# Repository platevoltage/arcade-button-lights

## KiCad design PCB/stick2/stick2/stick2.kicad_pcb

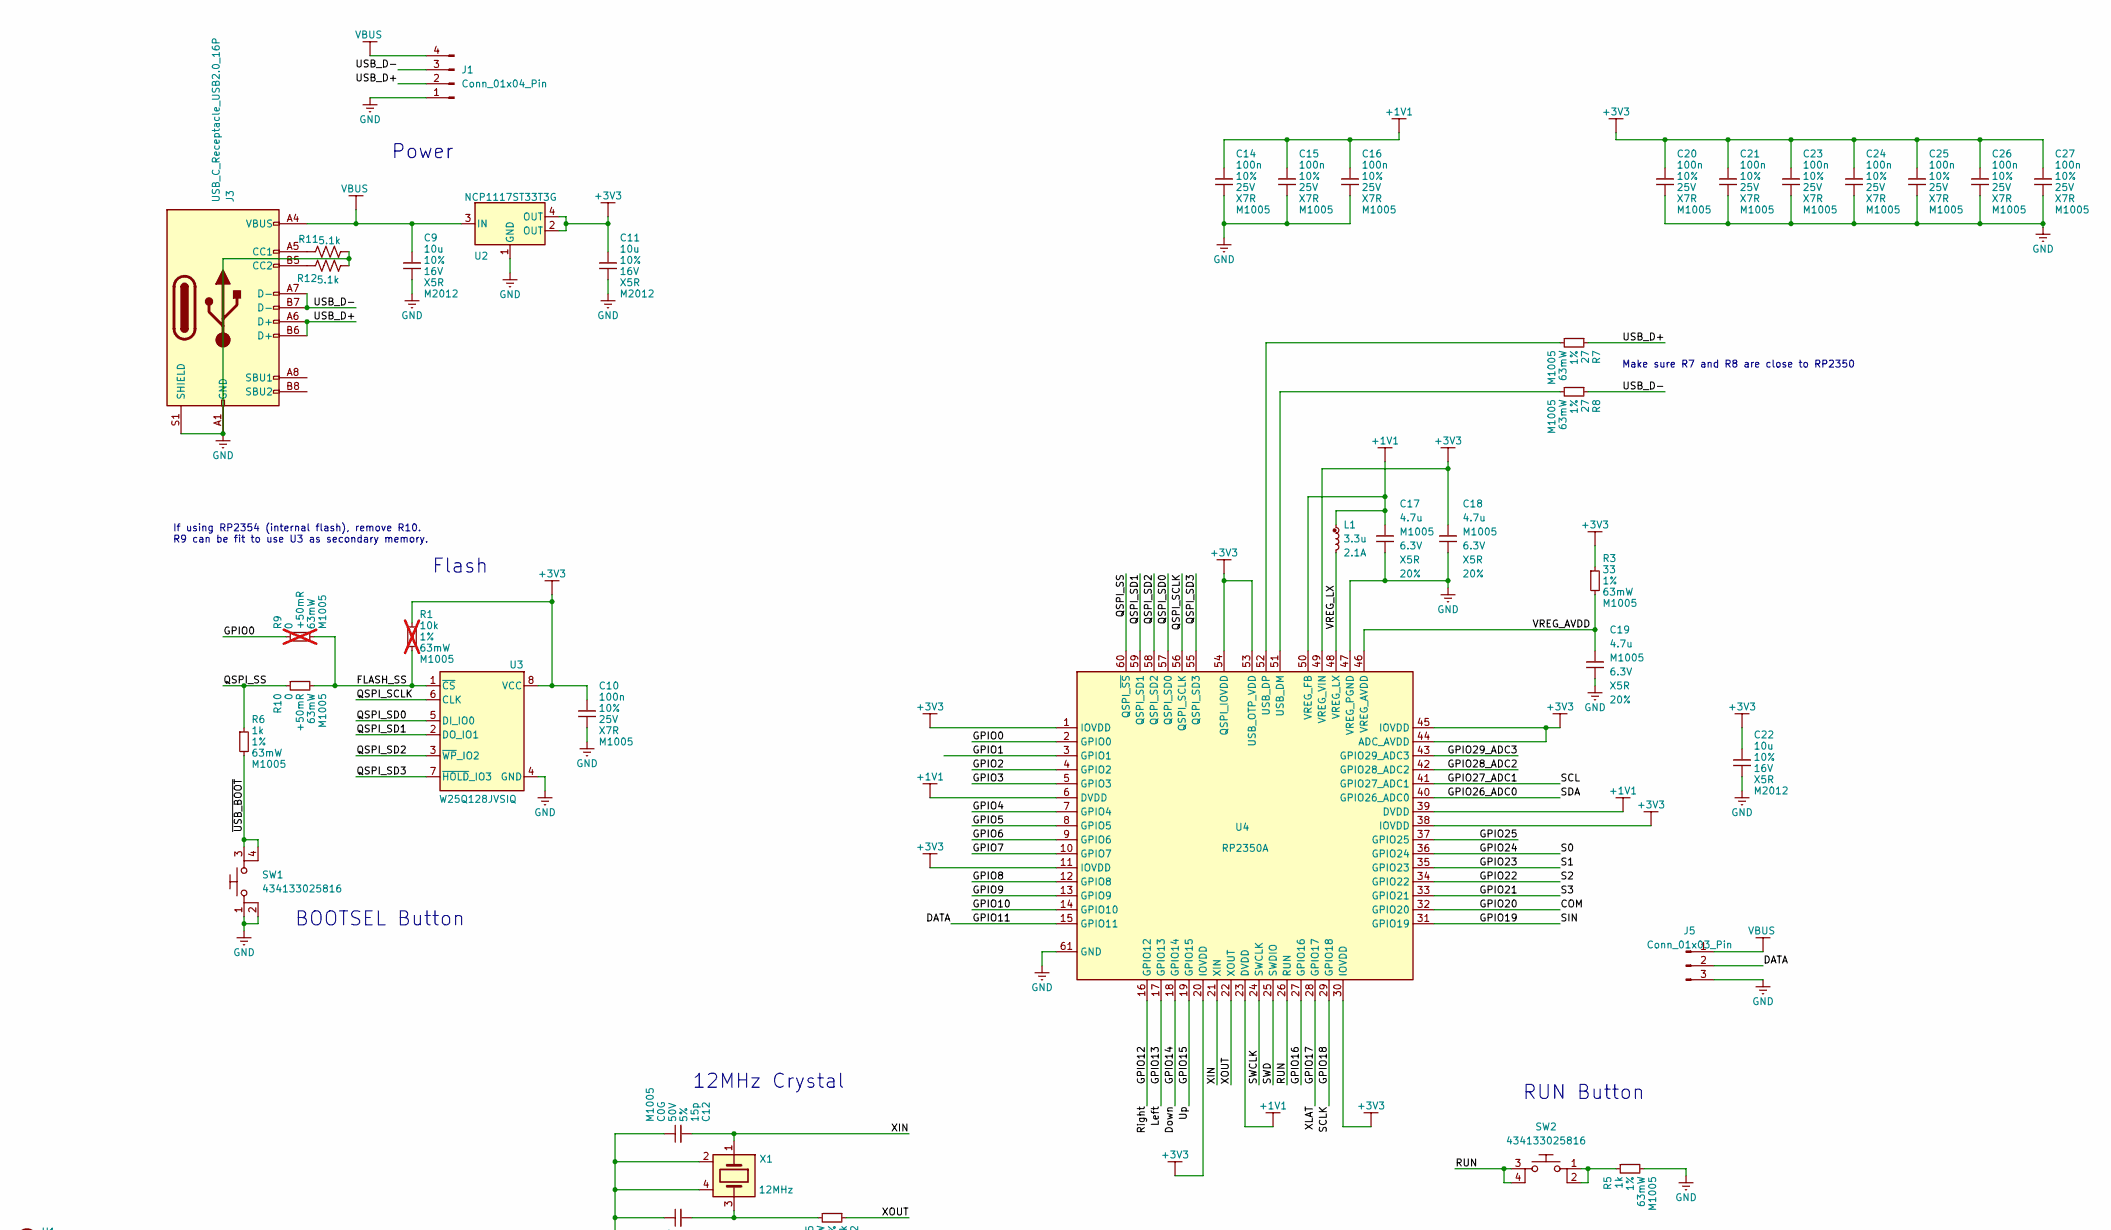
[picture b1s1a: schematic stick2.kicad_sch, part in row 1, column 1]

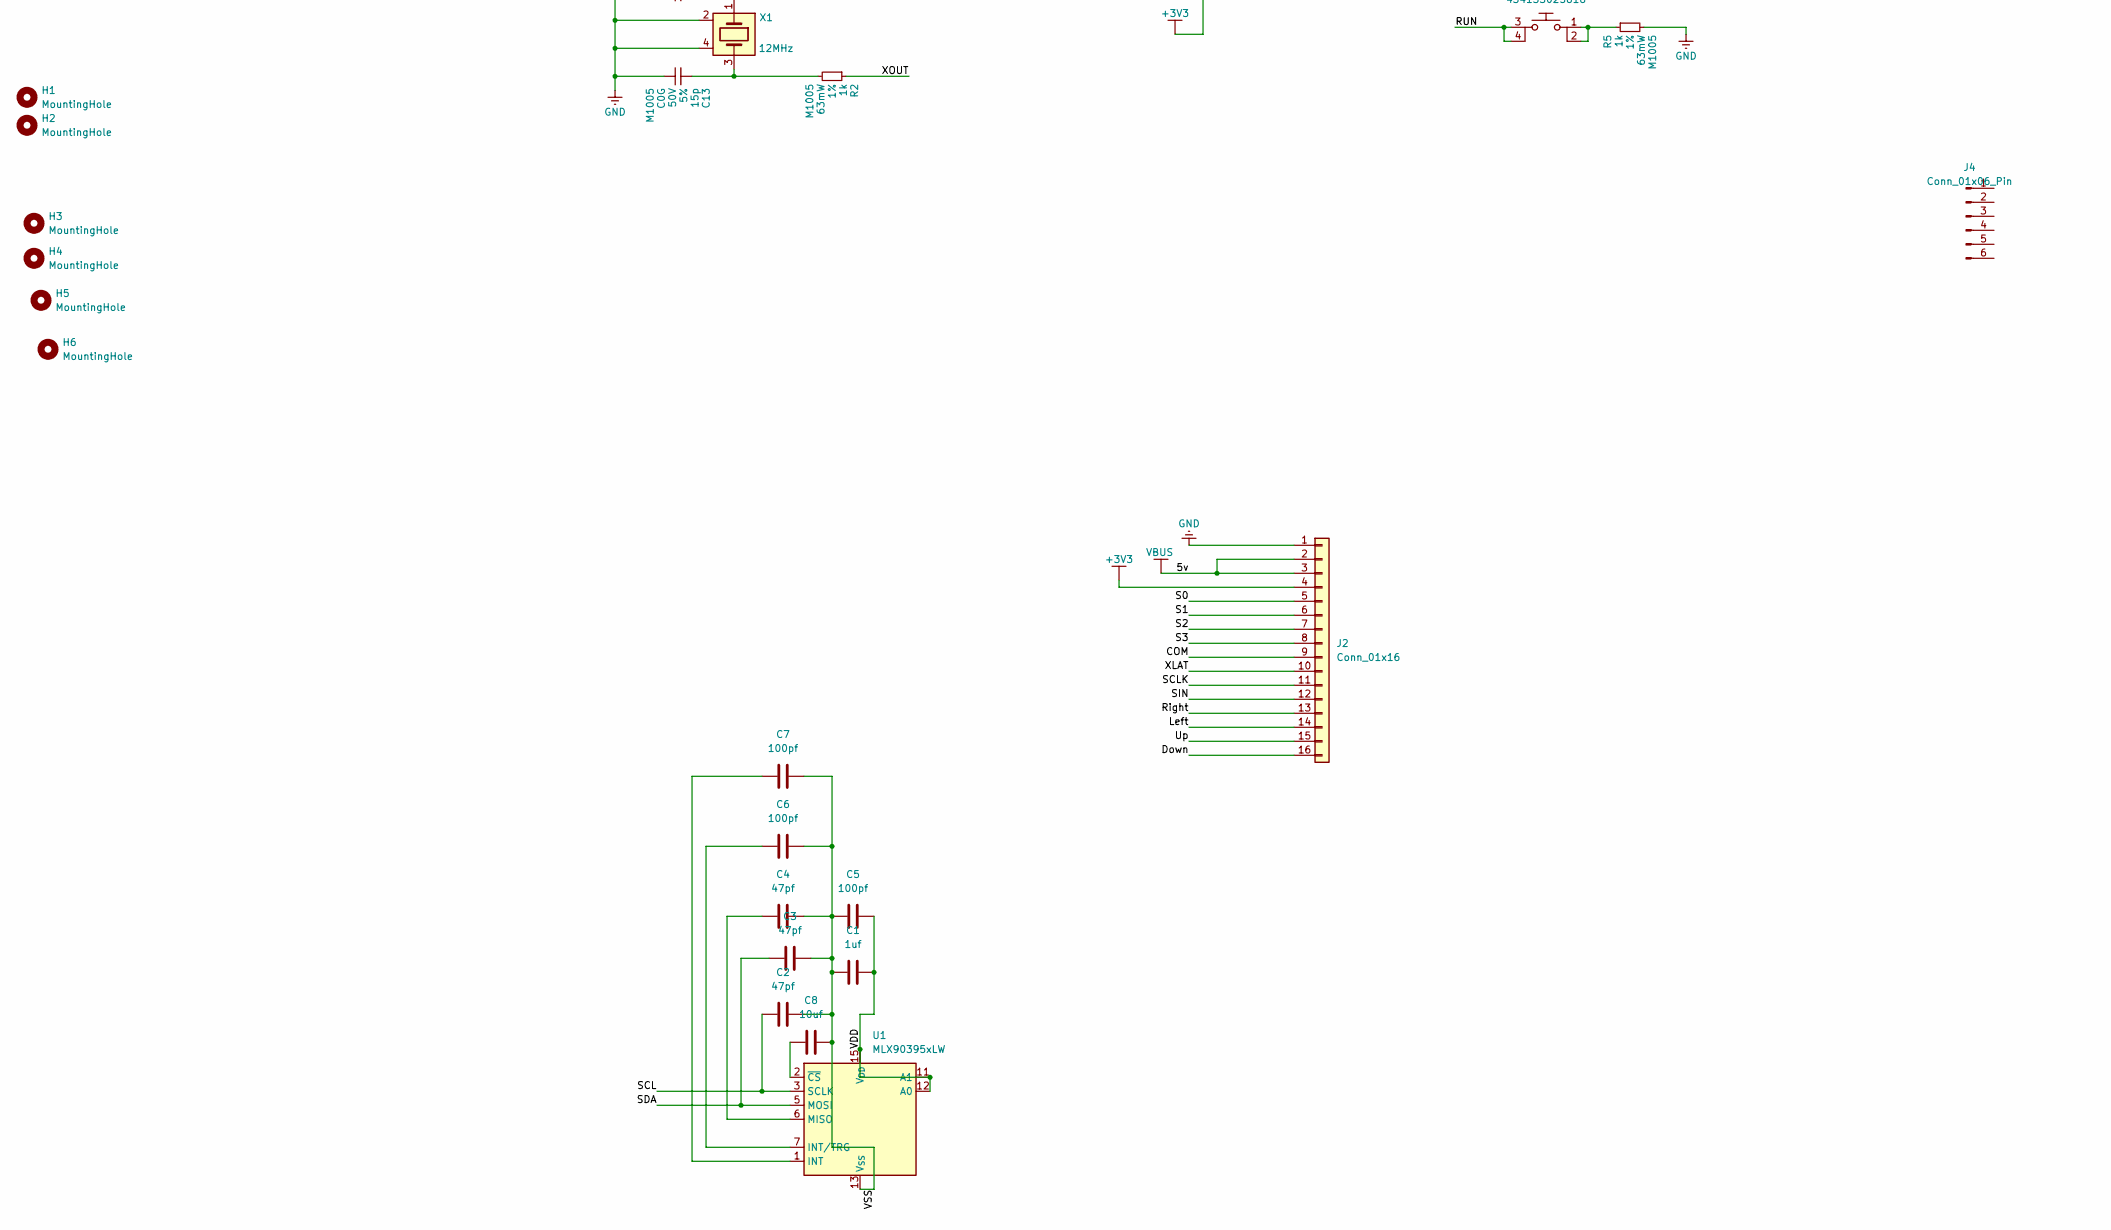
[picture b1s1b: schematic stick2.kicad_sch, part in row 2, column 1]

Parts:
C1: 1uf; C_0603_1608Metric_Pad1.08x0.95mm_HandSolder; MFR.Part # CC0603MRX5R5BB106; JLCPCB Part # C109454
C2, C3, C4: 47pf; C_0603_1608Metric_Pad1.08x0.95mm_HandSolder; MFR.Part # CC0603MRX5R5BB106; JLCPCB Part # C109454
C5, C6, C7: 100pf; C_0603_1608Metric_Pad1.08x0.95mm_HandSolder; MFR.Part # CC0603MRX5R5BB106; JLCPCB Part # C109454
C8: 10uf; C_0603_1608Metric_Pad1.08x0.95mm_HandSolder; MFR.Part # CC0603MRX5R5BB106; JLCPCB Part # C109454
C9, C11, C22: 10u; generic_capc2012x125; voltage 16V; tolerance 10%; part_uid RP-01GYSK-AVBE41; lcsc_pn C77075
C10, C14, C15, C16, C20, C21, C23, C24, C25, C26, C27: 100n; generic_capc1005x50; voltage 25V; tolerance 10%; part_uid RP-01BJ9Y-KRGF41; lcsc_pn C77014
C12, C13: 15p; generic_capc1005x50; voltage 50V; tolerance 5%; part_uid RP-01C89W-LLY9XV; lcsc_pn C77014
C17, C18: 4.7u; generic_capc1005x50_wide; voltage 6.3V; tolerance 20%; part_uid RP-019A1P-0C2GHY; lcsc_pn C82453
C19: 4.7u; generic_capc1005x50; voltage 6.3V; tolerance 20%; part_uid RP-019A1P-0C2GHY; lcsc_pn C77014
H1, H2: MountingHole; MountingHole_6mm
H3, H4, H5, H6: MountingHole; MountingHole_2.2mm_M2
J1: Conn_01x04_Pin; PinHeader_1x04_P2.54mm_Horizontal
J2: Conn_01x16; PinHeader_1x16_P2.54mm_Horizontal
J3: USB_C_Receptacle_USB2.0_16P; USB_C_Receptacle_GCT_USB4110
J4: Conn_01x06_Pin; PinHeader_1x06_P2.54mm_Horizontal
J5: Conn_01x03_Pin; PinHeader_1x03_P2.54mm_Horizontal
L1: 3.3u; abracon_aota-b201610s3r3-101-t; tolerance 20%; part_uid RP-01GY5D-2VC7WP; lcsc_pn C42411119
R1: 10k; generic_resc1005x35; tolerance 1%; voltage 50V; part_uid RP-019A1P-53DHSX; lcsc_pn C60490; not fitted
R2, R5, R6: 1k; generic_resc1005x35; tolerance 1%; voltage 50V; part_uid RP-019A1P-4Z6ZWY; lcsc_pn C60490
R3: 33; generic_resc1005x35; tolerance 1%; voltage 50V; part_uid RP-019A1P-58PW9L; lcsc_pn C60490
R7, R8: 27; generic_resc1005x35; tolerance 1%; voltage 50V; part_uid RP-01C89V-LTEYC4; lcsc_pn C60490
R9: 0; generic_resc1005x35; tolerance +50mR; voltage 50V; part_uid RP-019A1P-4Y4V63; lcsc_pn C60490; not fitted
R10: 0; generic_resc1005x35; tolerance +50mR; voltage 50V; part_uid RP-019A1P-4Y4V63; lcsc_pn C60490
R11, R12: 5.1k; R_0603_1608Metric_Pad0.98x0.95mm_HandSolder; MFR.Part # RC0603JR-075K1L; JLCPCB Part # C14677
SW1, SW2: 434133025816; wurthelek_434133025816; part_uid RP-01H0MT-6E9H8F
U1: MLX90395xLW; QFN-16-1EP_3x3mm_P0.5mm_EP1.675x1.675mm
U2: NCP1117ST33T3G; onsemi_ncp1117st33t3g; voltage 3.3V; part_uid RP-01JWD9-7JRX6J; lcsc_pn C26537
U3: W25Q128JVSIQ; generic_soic127p790x195-8; voltage 2.7-3.6V; part_uid RP-01JWD4-F1H4N9; lcsc_pn C97521
U4: RP2350A; rpi_rp2350a_vias; part_uid RP-01HA9H-9K5E8T; lcsc_pn C42411118
X1: 12MHz; generic_xtalcc320x250x80-4; tolerance 30ppm; part_uid RP-01G8X7-GS352B; lcsc_pn C20625731

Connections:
+1V1: C14.1, C15.1, C16.1, C17.1, L1.1, U4.6 (DVDD), U4.23 (DVDD), U4.39 (DVDD), U4.50 (VREG_FB)
+3V3: C10.1, C11.1, C18.1, C20.1, C21.1, C22.1, C23.1, C24.1, C25.1, C26.1, C27.1, J2.4, R1.1, R3.1, U2.2 (OUT), U2.4 (OUT), U3.8 (VCC), U4.1 (IOVDD), U4.11 (IOVDD), U4.20 (IOVDD), U4.30 (IOVDD), U4.38 (IOVDD), U4.44 (ADC_AVDD), U4.45 (IOVDD), U4.49 (VREG_VIN), U4.53 (USB_OTP_VDD), U4.54 (QSPI_IOVDD)
/COM: J2.9, U4.32 (GPIO20)
/DATA: J5.2, U4.15 (GPIO11)
/Down: J2.16, U4.18 (GPIO14)
/FLASH_SS: R1.2, R9.2, R10.2, U3.1 (~CS)
/GPIO0: R9.1, U4.2 (GPIO0)
/GPIO1: U4.3 (GPIO1)
/GPIO2: U4.4 (GPIO2)
/GPIO3: U4.5 (GPIO3)
/GPIO4: U4.7 (GPIO4)
/GPIO5: U4.8 (GPIO5)
/GPIO6: U4.9 (GPIO6)
/GPIO7: U4.10 (GPIO7)
/GPIO8: U4.12 (GPIO8)
/GPIO9: U4.13 (GPIO9)
/GPIO10: U4.14 (GPIO10)
/GPIO12: J2.13, U4.16 (GPIO12)
/GPIO13: J2.14, U4.17 (GPIO13)
/GPIO15: J2.15, U4.19 (GPIO15)
/GPIO16: U4.27 (GPIO16)
/GPIO17: J2.10, U4.28 (GPIO17)
/GPIO18: J2.11, U4.29 (GPIO18)
/GPIO19: J2.12, U4.31 (GPIO19)
/GPIO21: J2.8, U4.33 (GPIO21)
/GPIO22: J2.7, U4.34 (GPIO22)
/GPIO23: J2.6, U4.35 (GPIO23)
/GPIO24: J2.5, U4.36 (GPIO24)
/GPIO25: U4.37 (GPIO25)
/GPIO26_ADC0: C3.1, U1.5 (MOSI), U4.40 (GPIO26_ADC0)
/GPIO27_ADC1: C2.1, U1.3 (SCLK), U4.41 (GPIO27_ADC1)
/GPIO28_ADC2: U4.42 (GPIO28_ADC2)
/GPIO29_ADC3: U4.43 (GPIO29_ADC3)
/QSPI_SCLK: U3.6 (CLK), U4.56 (QSPI_SCLK)
/QSPI_SD0: U3.5 (DI_IO0), U4.57 (QSPI_SD0)
/QSPI_SD1: U3.2 (DO_IO1), U4.59 (QSPI_SD1)
/QSPI_SD2: U3.3 (~WP_IO2), U4.58 (QSPI_SD2)
/QSPI_SD3: U3.7 (~HOLD_IO3), U4.55 (QSPI_SD3)
/QSPI_SS: R6.1, R10.1, U4.60 (QSPI_~SS)
/RUN: SW2.3, SW2.4, U4.26 (RUN)
/SWCLK: U4.24 (SWCLK)
/SWD: U4.25 (SWDIO)
/USB_D+: J1.2, J3.A6 (D+), J3.B6 (D+), R7.1
/USB_D-: J1.3, J3.A7 (D-), J3.B7 (D-), R8.1
/VDD: C1.2, C5.1, U1.11 (A1), U1.12 (A0), U1.15 (V_{DD})
/VREG_AVDD: C19.1, R3.2, U4.46 (VREG_AVDD)
/VREG_LX: L1.2, U4.48 (VREG_LX)
/VSS: C1.1, C2.2, C3.2, C4.2, C5.2, C6.2, C7.2, C8.2, U1.4 (V_{SS}), U1.8 (V_{SS}), U1.9 (V_{SS}), U1.10 (V_{SS}), U1.13 (V_{SS}), U1.14 (V_{SS}), U1.16 (V_{SS}), U1.17 (V_{SS})
/XIN: C12.1, U4.21 (XIN), X1.1
/XOUT: R2.1, U4.22 (XOUT)
/~USB_BOOT: R6.2, SW1.3, SW1.4
GND: C9.2, C10.2, C11.2, C12.2, C13.2, C14.2, C15.2, C16.2, C17.2, C18.2, C19.2, C20.2, C21.2, C22.2, C23.2, C24.2, C25.2, C26.2, C27.2, J1.1, J2.1, J3.A1 (GND), J3.A12 (GND), J3.B1 (GND), J3.B12 (GND), J3.S1 (SHIELD), J5.3, R5.2, R11.2, R12.2, SW1.1, SW1.2, U2.1 (GND), U3.4 (GND), U4.47 (VREG_PGND), U4.61 (GND), X1.2, X1.4
unnamed: C13.1, R2.2, X1.3
unnamed: J3.A5 (CC1), R11.1
unnamed: J3.B5 (CC2), R12.1
unnamed: R5.1, SW2.1, SW2.2
unnamed: C7.1, U1.1 (INT)
unnamed: C6.1, U1.7 (INT/TRG)
unnamed: C4.1, U1.6 (MISO)
unnamed: C8.1, U1.2 (~CS)
unnamed: R8.2, U4.51 (USB_DM)
unnamed: R7.2, U4.52 (USB_DP)
VBUS: C9.1, J1.4, J2.2, J2.3, J3.A4 (VBUS), J3.A9 (VBUS), J3.B4 (VBUS), J3.B9 (VBUS), J5.1, U2.3 (IN)

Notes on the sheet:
Make sure R7 and R8 are close to RP2350
12MHz Crystal
Power
BOOTSEL Button
If using RP2354 (internal flash), remove R10. R9 can be fit to use U3 as secondary memory.
RUN Button
Flash

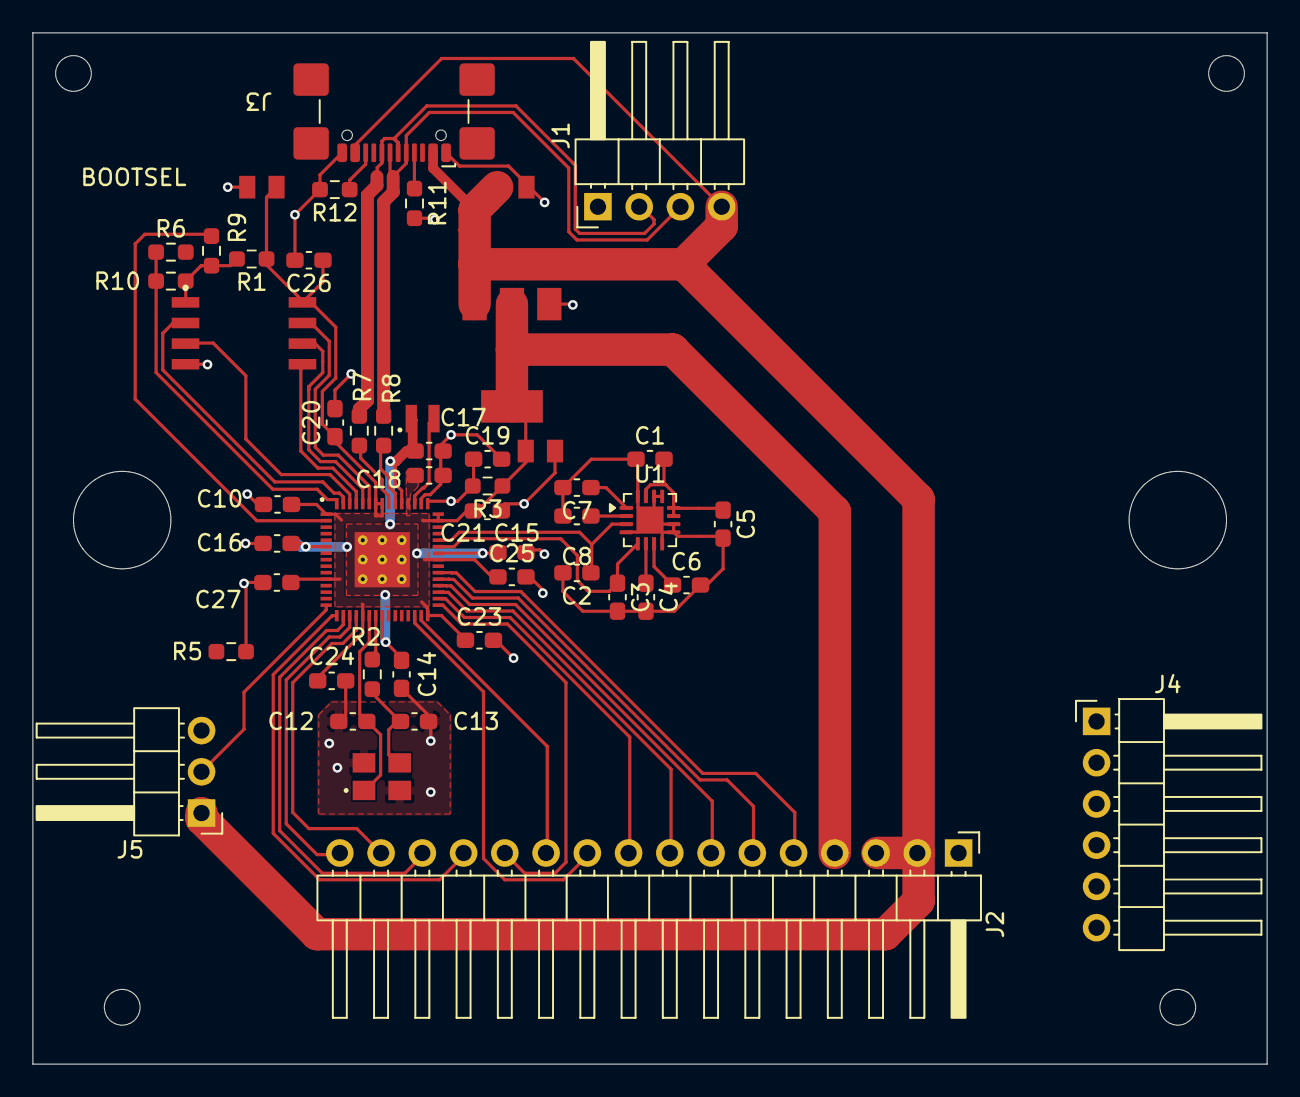
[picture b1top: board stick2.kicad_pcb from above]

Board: 2 copper layers, 76.0 x 63.5 mm, 55 parts (0 on the bottom side), 44 nets.

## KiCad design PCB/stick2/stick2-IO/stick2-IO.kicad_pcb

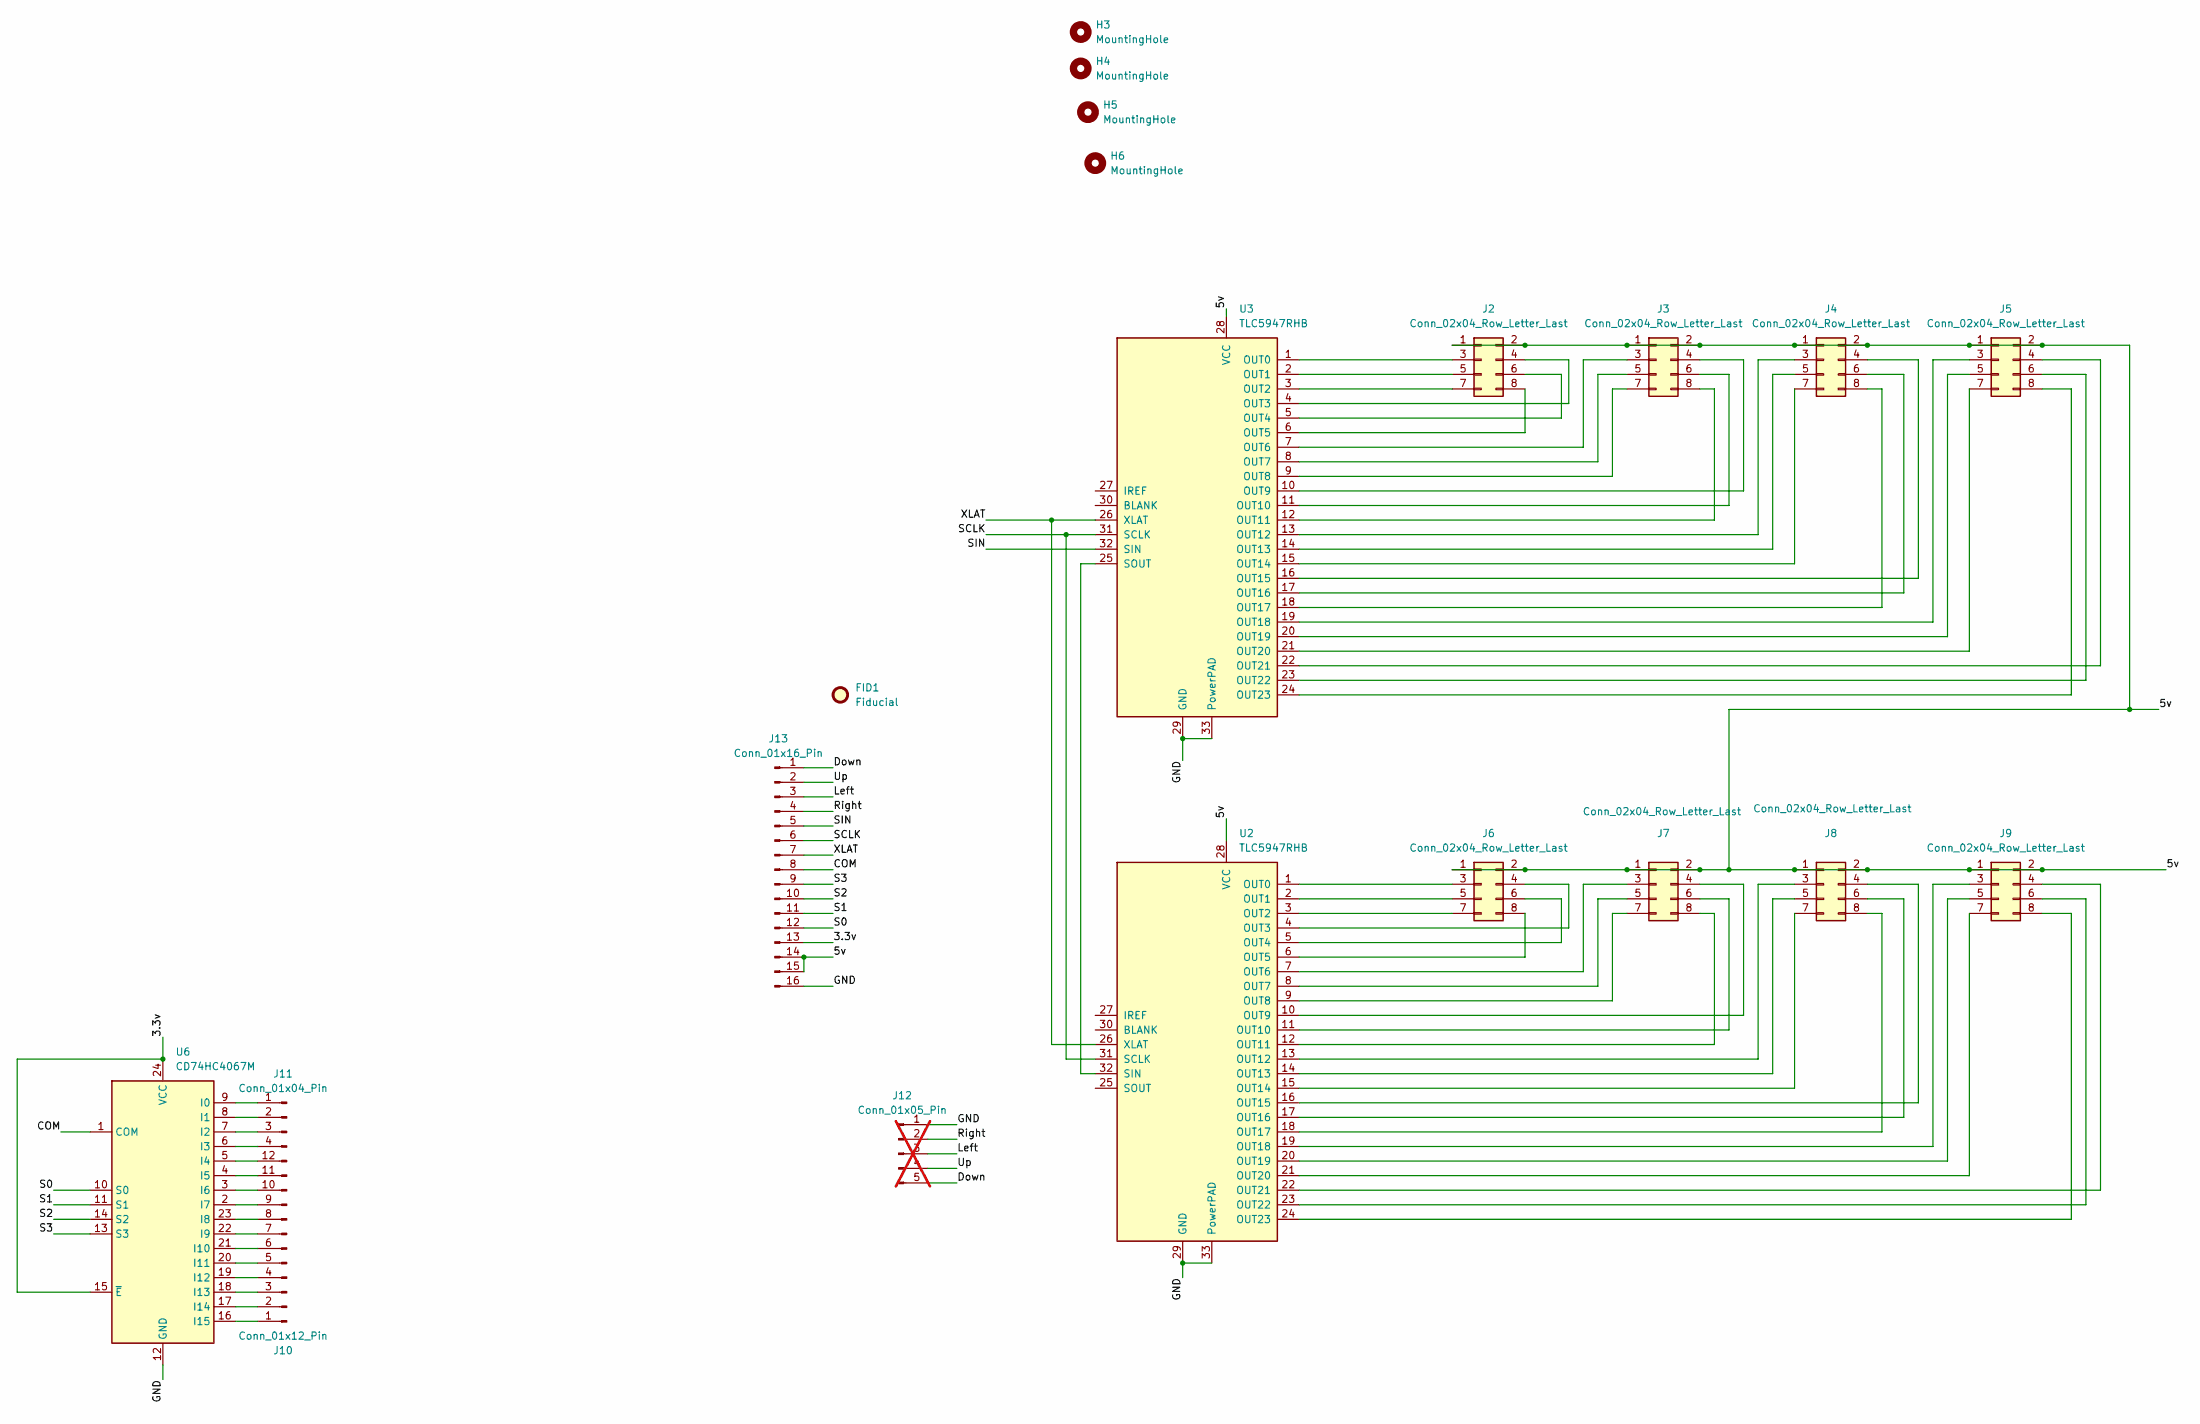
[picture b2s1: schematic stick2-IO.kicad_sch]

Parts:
FID1: Fiducial; Fiducial_0.5mm_Mask1mm
H3, H4, H5, H6: MountingHole; MountingHole_2.2mm_M2
J2, J3, J4, J5, J6, J7, J8, J9: Conn_02x04_Row_Letter_Last; PinHeader_2x04_P2.54mm_Vertical
J10: Conn_01x12_Pin; PinHeader_1x12_P2.54mm_Vertical
J11: Conn_01x04_Pin; PinHeader_1x04_P2.54mm_Vertical
J12: Conn_01x05_Pin; PinHeader_1x05_P2.54mm_Vertical; not fitted
J13: Conn_01x16_Pin; PinSocket_1x16_P2.54mm_Vertical
U2, U3: TLC5947RHB; QFN-32-1EP_5x5mm_P0.5mm_EP3.45x3.45mm
U6: CD74HC4067M; SSOP-24_5.3x8.2mm_P0.65mm

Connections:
/3.3v: J13.13, U6.15 (~E), U6.24 (VCC)
/5v: J2.1, J2.2, J3.1, J3.2, J4.1, J4.2, J5.1, J5.2, J6.1, J6.2, J7.1, J7.2, J8.1, J8.2, J9.1, J9.2, J13.14, J13.15, U2.28 (VCC), U3.28 (VCC)
/COM: J13.8, U6.1 (COM)
/Down: J12.5, J13.1
/GND: J12.1, J13.16, U2.29 (GND), U2.33 (PowerPAD), U3.29 (GND), U3.33 (PowerPAD), U6.12 (GND)
/Left: J12.3, J13.3
/Right: J12.2, J13.4
/S0: J13.12, U6.10 (S0)
/S1: J13.11, U6.11 (S1)
/S2: J13.10, U6.14 (S2)
/S3: J13.9, U6.13 (S3)
/SCLK: J13.6, U2.31 (SCLK), U3.31 (SCLK)
/SIN: J13.5, U3.32 (SIN)
/Up: J12.4, J13.2
/XLAT: J13.7, U2.26 (XLAT), U3.26 (XLAT)
unnamed: J2.3, U3.1 (OUT0)
unnamed: J2.4, U3.4 (OUT3)
unnamed: J2.5, U3.2 (OUT1)
unnamed: J2.6, U3.5 (OUT4)
unnamed: J2.7, U3.3 (OUT2)
unnamed: J2.8, U3.6 (OUT5)
unnamed: J3.3, U3.7 (OUT6)
unnamed: J3.4, U3.10 (OUT9)
unnamed: J3.5, U3.8 (OUT7)
unnamed: J3.6, U3.11 (OUT10)
unnamed: J3.7, U3.9 (OUT8)
unnamed: J3.8, U3.12 (OUT11)
unnamed: J4.3, U3.13 (OUT12)
unnamed: J4.4, U3.16 (OUT15)
unnamed: J4.5, U3.14 (OUT13)
unnamed: J4.6, U3.17 (OUT16)
unnamed: J4.7, U3.15 (OUT14)
unnamed: J4.8, U3.18 (OUT17)
unnamed: J5.3, U3.19 (OUT18)
unnamed: J5.4, U3.22 (OUT21)
unnamed: J5.5, U3.20 (OUT19)
unnamed: J5.6, U3.23 (OUT22)
unnamed: J5.7, U3.21 (OUT20)
unnamed: J5.8, U3.24 (OUT23)
unnamed: J6.3, U2.1 (OUT0)
unnamed: J6.4, U2.4 (OUT3)
unnamed: J6.5, U2.2 (OUT1)
unnamed: J6.6, U2.5 (OUT4)
unnamed: J6.7, U2.3 (OUT2)
unnamed: J6.8, U2.6 (OUT5)
unnamed: J7.3, U2.7 (OUT6)
unnamed: J7.4, U2.10 (OUT9)
unnamed: J7.5, U2.8 (OUT7)
unnamed: J7.6, U2.11 (OUT10)
unnamed: J7.7, U2.9 (OUT8)
unnamed: J7.8, U2.12 (OUT11)
unnamed: J8.3, U2.13 (OUT12)
unnamed: J8.4, U2.16 (OUT15)
unnamed: J8.5, U2.14 (OUT13)
unnamed: J8.6, U2.17 (OUT16)
unnamed: J8.7, U2.15 (OUT14)
unnamed: J8.8, U2.18 (OUT17)
unnamed: J9.3, U2.19 (OUT18)
unnamed: J9.4, U2.22 (OUT21)
unnamed: J9.5, U2.20 (OUT19)
unnamed: J9.6, U2.23 (OUT22)
unnamed: J9.7, U2.21 (OUT20)
unnamed: J9.8, U2.24 (OUT23)
unnamed: J10.1, U6.16 (I15)
unnamed: J10.2, U6.17 (I14)
unnamed: J10.3, U6.18 (I13)
unnamed: J10.4, U6.19 (I12)
unnamed: J10.5, U6.20 (I11)
unnamed: J10.6, U6.21 (I10)
unnamed: J10.7, U6.22 (I9)
unnamed: J10.8, U6.23 (I8)
unnamed: J10.9, U6.2 (I7)
unnamed: J10.10, U6.3 (I6)
unnamed: J10.11, U6.4 (I5)
unnamed: J10.12, U6.5 (I4)
unnamed: J11.1, U6.9 (I0)
unnamed: J11.2, U6.8 (I1)
unnamed: J11.3, U6.7 (I2)
unnamed: J11.4, U6.6 (I3)
unnamed: U2.32 (SIN), U3.25 (SOUT)

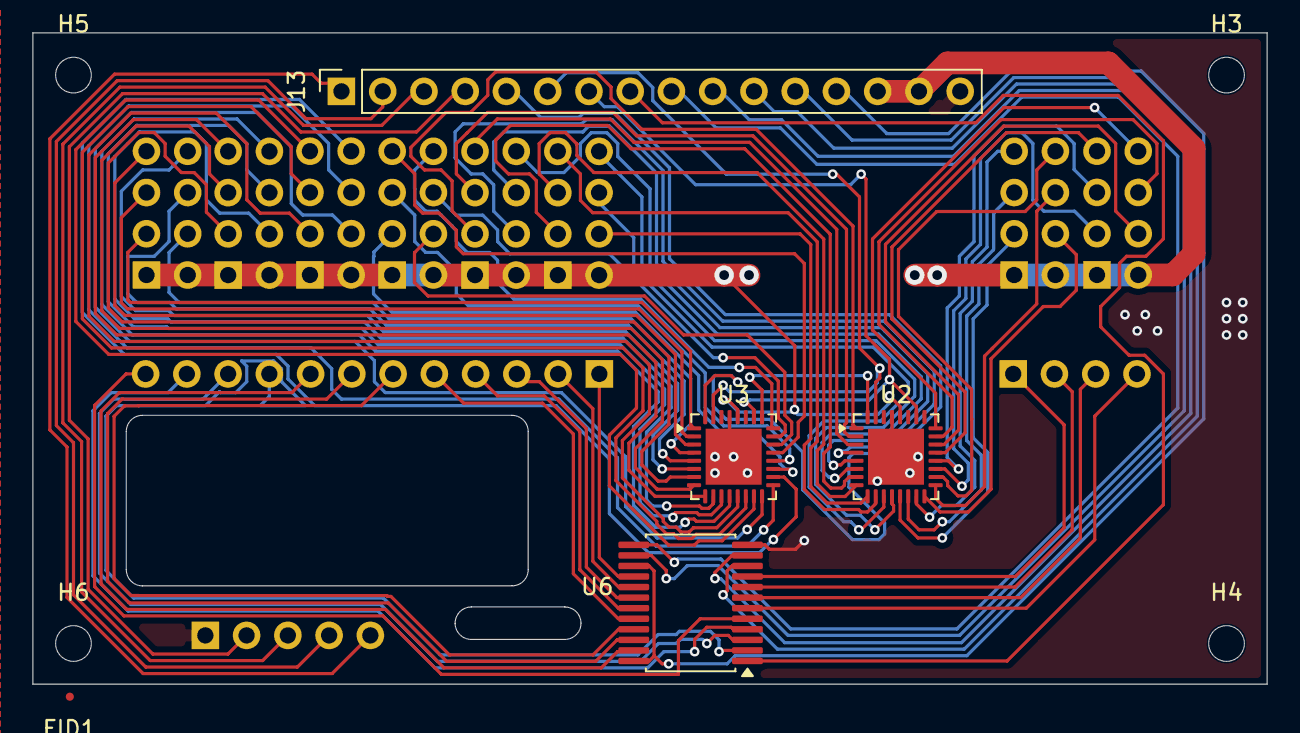
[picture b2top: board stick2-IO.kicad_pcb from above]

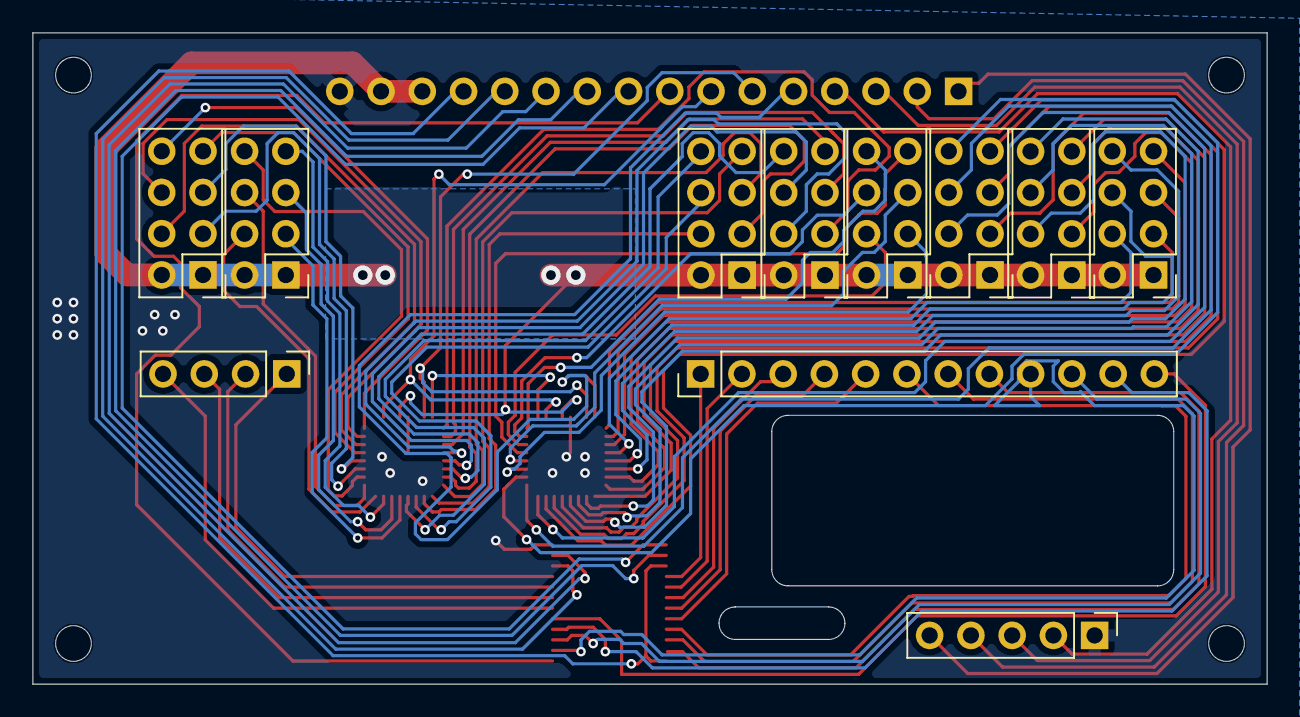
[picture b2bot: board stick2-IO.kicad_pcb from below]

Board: 2 copper layers, 76.0 x 40.1 mm, 20 parts (11 on the bottom side), 80 nets.
